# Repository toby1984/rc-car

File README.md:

# RC car 

This project consists of a very crude "RC car" plus a 433 Mhz remote control (both driven by Arduino Nanos).

Since this is a fun project I didn't use any ready-made libraries at all (apart from the AVR libc) and the project builds with old-fashioned 'make' and does not use the Arduino IDE. You'll need a working linux avr-gcc installation and some ISP programmer to upload the firmware.

## Parts list

- some cardboard as base plate of the car (I had to glue together 2-3 layers to make it stiff enough)
- 2x Arduino Nano (~3€/pc)
- 1x 433 Mhz sender module with antenna (PCB has HFY-J1B printed on it, 1.40 €/pc))
- 1x 433 Mhz receiver module with antenna (RXB6 SuperHet, 2.50 €/pc)
- 2x helical 433 Mhz antenna ( 0.50€/pc)
- 2xAA battery holder  (~1€/pc)
- 4xAA battery holder (~1€/pc)
- 2x JGA25-370 6V DC motors, 133 RPM, with built-in encoders ( hard to find with encoders, ~11€/pc)
- 2x wheels, ball caster, 2x shaft coupling, 2x DC motor mounting brackets, screws (I bought a kit that included all of this plus 2 JGA25-370 motors for 15€, didn't use the motors though...)
- 2x 5V Step-Up/Step-Down converter (Pololu S9V11F5 , 4.79€/pc)
- 2-axis joystick module ( 3€/pc )
- DRV8833 module for driving the DC motors (3.00€/pc)

Total cost: A whopping 65€, ouch!

I think you can get this down to around ~40€ (go for cheaper motors without encoders,use no or lower-power step-up/step down converters and find cheap wheels, ball castermshaft couplings+mounting brackets) but given the fact that you can grab RC cars at your local toy store for much less it's obvious that this is never going to compete cost-wise.

## Radio remote pinout (Atmega328p)

The remote is designed to run on an ATPega328p with the radio module and joystick connected as follows:

### Joystick

X AXIS - ADC1
Y AXIS - ADC0

NOTE: Depending on the joystick you're using you might need to adjust the min/max and center values in joystick.c

### Radio

RF DATA OUT - D2

## RC car pinout (Atmega2560)

### Power

RC car will be powered as long as B0 stays HIGH.

### Radio

RF DATA IN - D7

### Motor driver

Wiring:

ORANGE (IN1),YELLOW (IN2) -> Left motor
RED (IN3),GREEN (IN4) -> Right motor

Pinout:
Left motor: OC0A and OC0B
Right motor: OC2A and OC2B

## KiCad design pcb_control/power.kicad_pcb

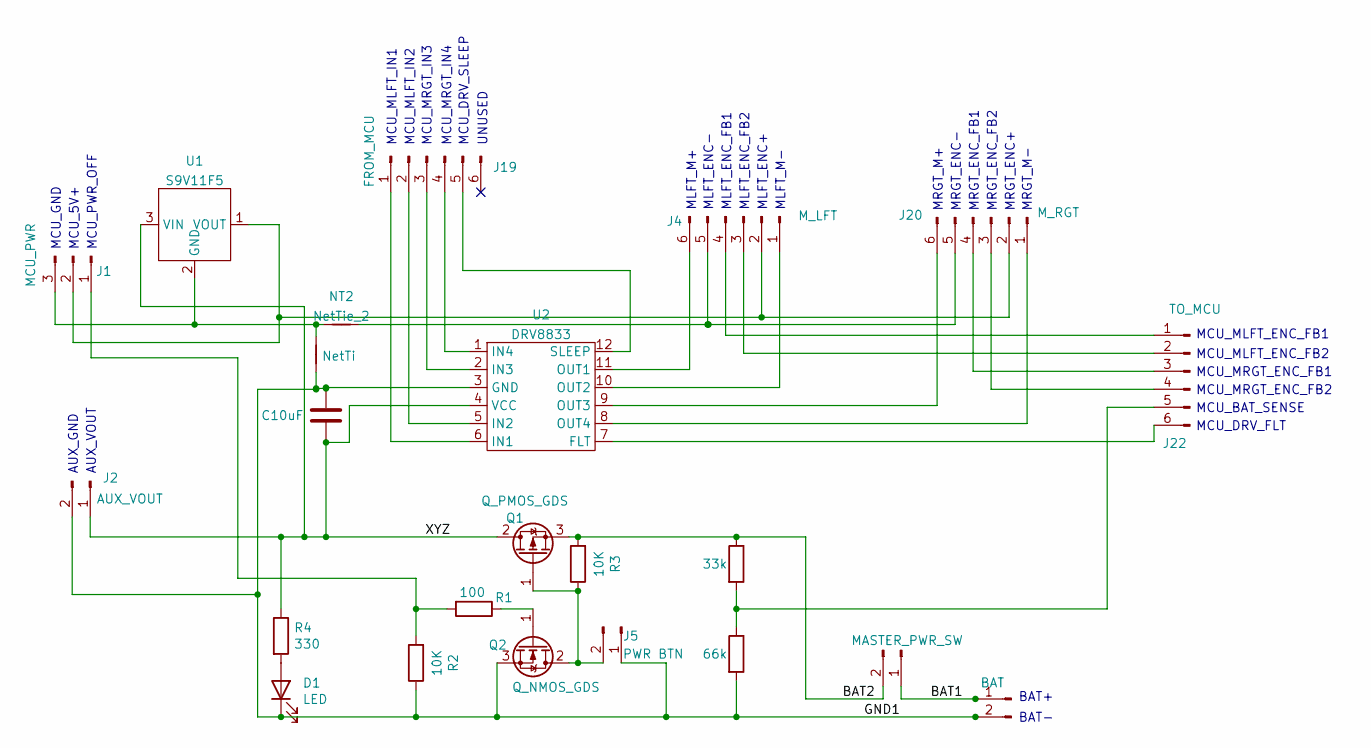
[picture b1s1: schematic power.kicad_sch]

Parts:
C1: C10uF; C_Radial_D5.0mm_H11.0mm_P2.00mm
D1: LED; LED_D5.0mm
J1: MCU_PWR; JST_XH_B3B-XH-A_1x03_P2.50mm_Vertical
J2: AUX_VOUT; JST_XH_B2B-XH-A_1x02_P2.50mm_Vertical
J4: M_LFT; JST_XH_S6B-XH-A_1x06_P2.50mm_Horizontal
J5: PWR BTN; JST_XH_B2B-XH-A_1x02_P2.50mm_Vertical
J6: MASTER_PWR_SW; JST_XH_B2B-XH-A_1x02_P2.50mm_Vertical
J19: FROM_MCU; JST_XH_B6B-XH-A_1x06_P2.50mm_Vertical
J20: M_RGT; JST_XH_S6B-XH-A_1x06_P2.50mm_Horizontal
J21: BAT; JST_XH_S2B-XH-A-1_1x02_P2.50mm_Horizontal
J22: TO_MCU; JST_XH_B6B-XH-A_1x06_P2.50mm_Vertical
NT1: NetTi; NetTie-2_SMD_Pad2.0mm
NT2: NetTie_2; NetTie-2_SMD_Pad2.0mm
Q1: Q_PMOS_GDS; TO-220-3_Vertical
Q2: Q_NMOS_GDS; TO-220-3_Vertical
R1: 100; R_Axial_DIN0207_L6.3mm_D2.5mm_P10.16mm_Horizontal
R2, R3: 10K; R_Axial_DIN0207_L6.3mm_D2.5mm_P10.16mm_Horizontal
R4: 330; R_Axial_DIN0207_L6.3mm_D2.5mm_P10.16mm_Horizontal
R5: 33k; R_Axial_DIN0207_L6.3mm_D2.5mm_P10.16mm_Horizontal
R6: 66k; R_Axial_DIN0207_L6.3mm_D2.5mm_P10.16mm_Horizontal
U1: S9V11F5; pololu_5v_updown
U2: DRV8833; drv8833

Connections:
/BAT1: J6.1, J21.1
/BAT2: J6.2, Q1.3 (S), R3.2, R5.1
/GND1: C1.1, D1.1 (K), J2.2, J5.1, J21.2, NT1.1, Q2.3 (S), R2.1, R6.2, U2.3 (GND)
/XYZ: C1.2, J2.1, Q1.2 (D), R4.1, U1.3 (VIN), U2.4 (VCC)
unnamed: D1.2 (A), R4.2
unnamed: J1.1, R1.2, R2.2
unnamed: J1.2, J4.2, J20.2, U1.1 (VOUT)
unnamed: J1.3, NT1.2, NT2.1, U1.2 (GND)
unnamed: J4.1, U2.10 (OUT2)
unnamed: J4.6, U2.11 (OUT1)
unnamed: J5.2, Q1.1 (G), Q2.2 (D), R3.1
unnamed: J19.1, U2.6 (IN1)
unnamed: J19.2, U2.5 (IN2)
unnamed: J19.3, U2.2 (IN3)
unnamed: J19.4, U2.1 (IN4)
unnamed: J19.5, U2.12 (SLEEP)
unnamed: J20.1, U2.8 (OUT4)
unnamed: J20.3, J22.4
unnamed: J20.4, J22.3
unnamed: J4.5, J20.5, NT2.2
unnamed: J20.6, U2.9 (OUT3)
unnamed: J4.4, J22.1
unnamed: J4.3, J22.2
unnamed: J22.5, R5.2, R6.1
unnamed: J22.6, U2.7 (FLT)
unnamed: Q2.1 (G), R1.1

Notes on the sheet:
MCU_MRGT_ENC_FB1
MCU_MRGT_IN3
MRGT_ENC_FB1
MCU_PWR_OFF
MCU_DRV_FLT
UNUSED
MRGT_ENC-
MLFT_ENC_FB2
BAT-
AUX_VOUT
MLFT_ENC_FB1
MLFT_M-
MLFT_ENC-
MLFT_M+
MCU_5V+
MCU_MLFT_IN2
MRGT_M+
MLFT_ENC+
MCU_MRGT_IN4
MCU_MLFT_ENC_FB2
MCU_BAT_SENSE
MCU_MRGT_ENC_FB2
MCU_MLFT_IN1
MCU_GND
MRGT_M-
AUX_GND
MRGT_ENC_FB2
MRGT_ENC+
MCU_DRV_SLEEP
BAT+
MCU_MLFT_ENC_FB1

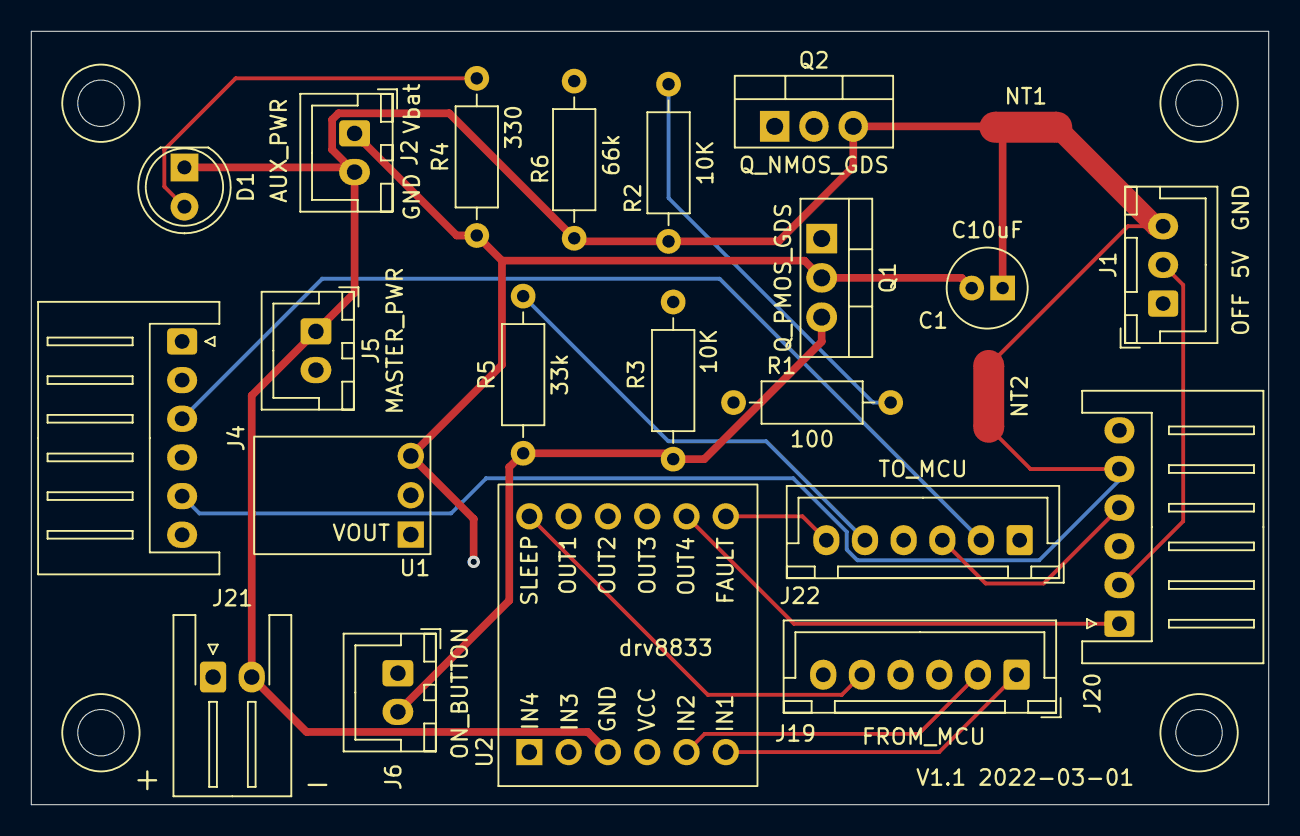
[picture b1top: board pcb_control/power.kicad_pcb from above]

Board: 4 copper layers, 80.0 x 50.0 mm, 23 parts (0 on the bottom side), 26 nets.

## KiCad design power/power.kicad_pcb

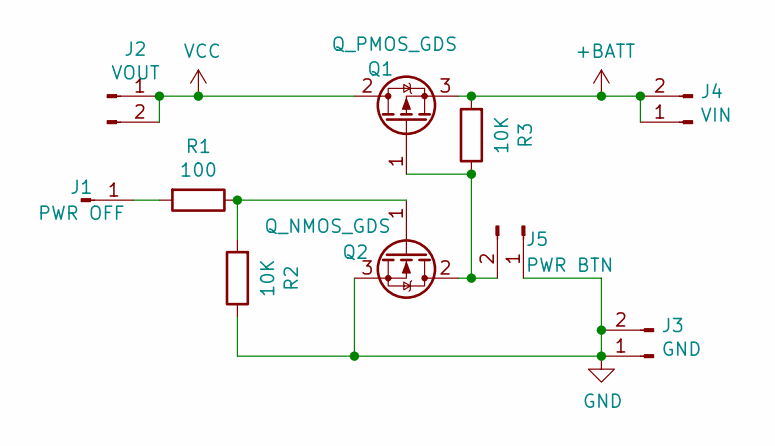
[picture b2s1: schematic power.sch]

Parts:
J1: PWR OFF; PinHeader_1x01_P2.54mm_Vertical
J2: VOUT; PinHeader_1x02_P2.54mm_Vertical
J3: GND; PinHeader_1x02_P2.54mm_Vertical
J4: VIN; PinHeader_1x02_P2.54mm_Vertical
J5: PWR BTN; PinHeader_1x02_P2.54mm_Vertical
Q1: Q_PMOS_GDS; TO-220-3_Vertical
Q2: Q_NMOS_GDS; TO-220-3_Vertical
R1: 100; R_Axial_DIN0207_L6.3mm_D2.5mm_P10.16mm_Horizontal
R2, R3: 10K; R_Axial_DIN0207_L6.3mm_D2.5mm_P10.16mm_Horizontal

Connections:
+BATT: J4.1, J4.2, Q1.3 (S), R3.2
GND: J3.1, J3.2, J5.1, Q2.3 (S), R2.1
unnamed: J1.1, R1.2
unnamed: J5.2, Q1.1 (G), Q2.2 (D), R3.1
unnamed: Q2.1 (G), R1.1, R2.2
VCC: J2.1, J2.2, Q1.2 (D)

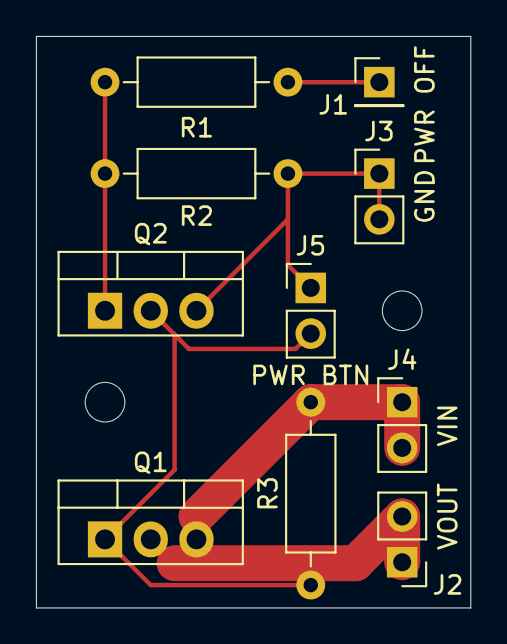
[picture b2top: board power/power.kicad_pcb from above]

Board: 2 copper layers, 24.1 x 31.8 mm, 10 parts (0 on the bottom side), 6 nets.

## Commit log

2020-12-14 added reading of joystick X/Y potentiometers
2020-12-23 bugfixes
2020-12-23 removed
2021-01-13 added support for having 16-bit timer trigger an IRQ after a specific microseconds interval
2021-01-13 started work on I2C to have a second arduino perform the radio communication
2021-02-01 added KiCAD files
2021-04-07 added case FreeCad
2021-07-31 fixed X/Y axis mapping calculation in joystick.c
2021-08-02 added support for automatically powering down after 2 minutes
2021-08-19 re-wrote I2C sending to be interrupt-driven
2022-06-06 refactored src layout so remote can run on ATmega328p while rest uses ATmega2560
2022-06-06 added symlinks
2022-06-06 code cleanup
2022-06-06 documentation
2022-06-06 adjusted ADC max value, for some reason the ADC does not reach the 1023 maximum reading
